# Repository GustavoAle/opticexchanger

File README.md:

# OpticExchanger 
## A bare metal optic fiber data transmission software

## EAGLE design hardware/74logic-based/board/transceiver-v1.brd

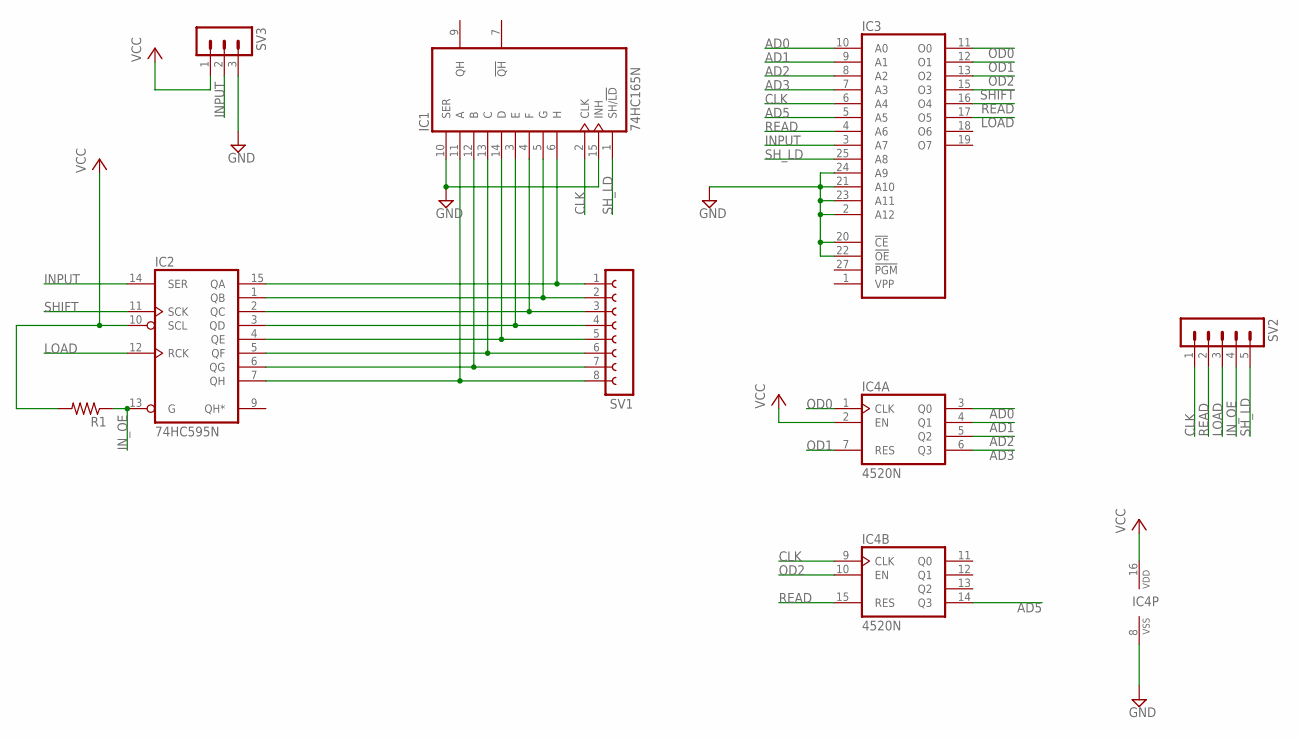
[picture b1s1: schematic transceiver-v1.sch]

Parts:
IC1: 74HC165N; DIL16
IC2: 74HC595N; DIL16
IC3: 2764; DIL28
IC4: 4520N; DIL16
R1: R-US_0207/10; 0207/10
SV1: FE08-1; FE08
SV2: MA05-1
SV3: MA03-1

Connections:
AD0: IC3.10 (A0), IC4.3 (Q0)
AD1: IC3.9 (A1), IC4.4 (Q1)
AD2: IC3.8 (A2), IC4.5 (Q2)
AD3: IC3.7 (A3), IC4.6 (Q3)
AD5: IC3.5 (A5), IC4.14 (Q3)
CLK: IC1.2 (CLK), IC3.6 (A4), IC4.9 (CLK), SV2.1
GND: IC1.8 (GND), IC1.10 (SER), IC1.15 (INH), IC2.8 (GND), IC3.2 (A12), IC3.14 (GND), IC3.20 (!CE), IC3.21 (A10), IC3.22 (!OE), IC3.23 (A11), IC3.24 (A9), IC4.8 (VSS), SV3.3
INPUT: IC2.14 (SER), IC3.3 (A7), SV3.2
IN_OE: IC2.13 (G), R1.1, SV2.4
LOAD: IC2.12 (RCK), IC3.17 (O5), SV2.3
unnamed: IC1.6 (H), IC2.15 (QA), SV1.1
unnamed: IC1.5 (G), IC2.1 (QB), SV1.2
unnamed: IC1.4 (F), IC2.2 (QC), SV1.3
unnamed: IC1.3 (E), IC2.3 (QD), SV1.4
unnamed: IC1.14 (D), IC2.4 (QE), SV1.5
unnamed: IC1.13 (C), IC2.5 (QF), SV1.6
unnamed: IC1.12 (B), IC2.6 (QG), SV1.7
unnamed: IC1.11 (A), IC2.7 (QH), SV1.8
OD0: IC3.11 (O0), IC4.1 (CLK)
OD1: IC3.12 (O1), IC4.7 (RES)
OD2: IC3.13 (O2), IC4.10 (EN)
READ: IC3.4 (A6), IC3.16 (O4), IC4.15 (RES), SV2.2
SHIFT: IC2.11 (SCK), IC3.15 (O3)
SH_LD: IC1.1 (SH/!LD), IC3.25 (A8), SV2.5
VCC: IC1.16 (VCC), IC2.10 (SCL), IC2.16 (VCC), IC3.28 (VCC), IC4.2 (EN), IC4.16 (VDD), R1.2, SV3.1

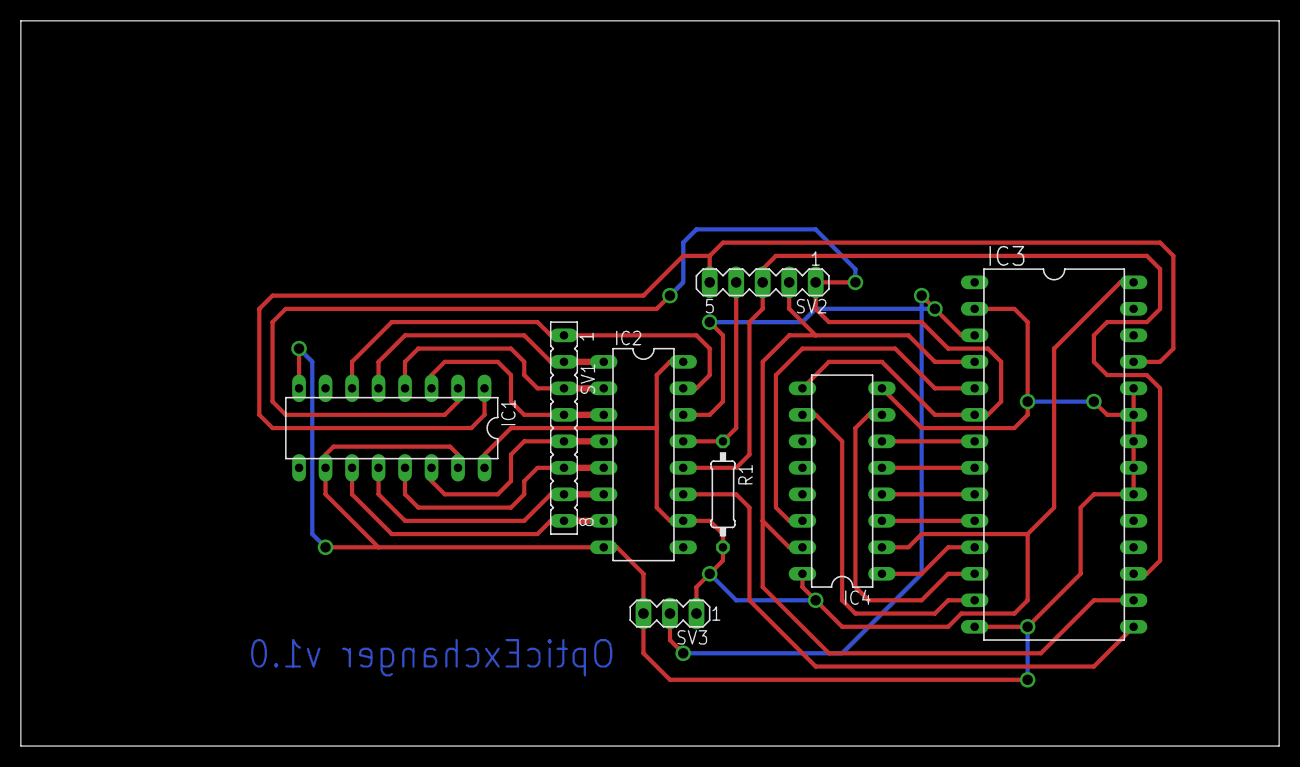
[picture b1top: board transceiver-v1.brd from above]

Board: 2 copper layers, 120.6 x 69.5 mm, 8 parts (0 on the bottom side), 25 nets.

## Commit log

2019-10-24 first
2019-10-28 Aesthetic updates
2019-10-28 added new theme
2019-10-28 added theme 2
2019-10-30 serial wrapper created
2019-10-30 license and readme
2019-11-02 added logos, removed gtk.css due to license incompatibility
2020-03-22 First commit v1.0
